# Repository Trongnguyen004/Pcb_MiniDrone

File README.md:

# Pcb_MiniDrone
### #Hình ảnh

<p align="center">
  <table>
    <tr>
      <td>
        
      </td>
      <td>
        
      </td>
    </tr>
  </table>
</p>

### #3D

<p align="center">
  <table>
    <tr>
      <td>
        
      </td>
      <td>
        
      </td>
      <td>
        
      </td>
    </tr>
  </table>
</p>

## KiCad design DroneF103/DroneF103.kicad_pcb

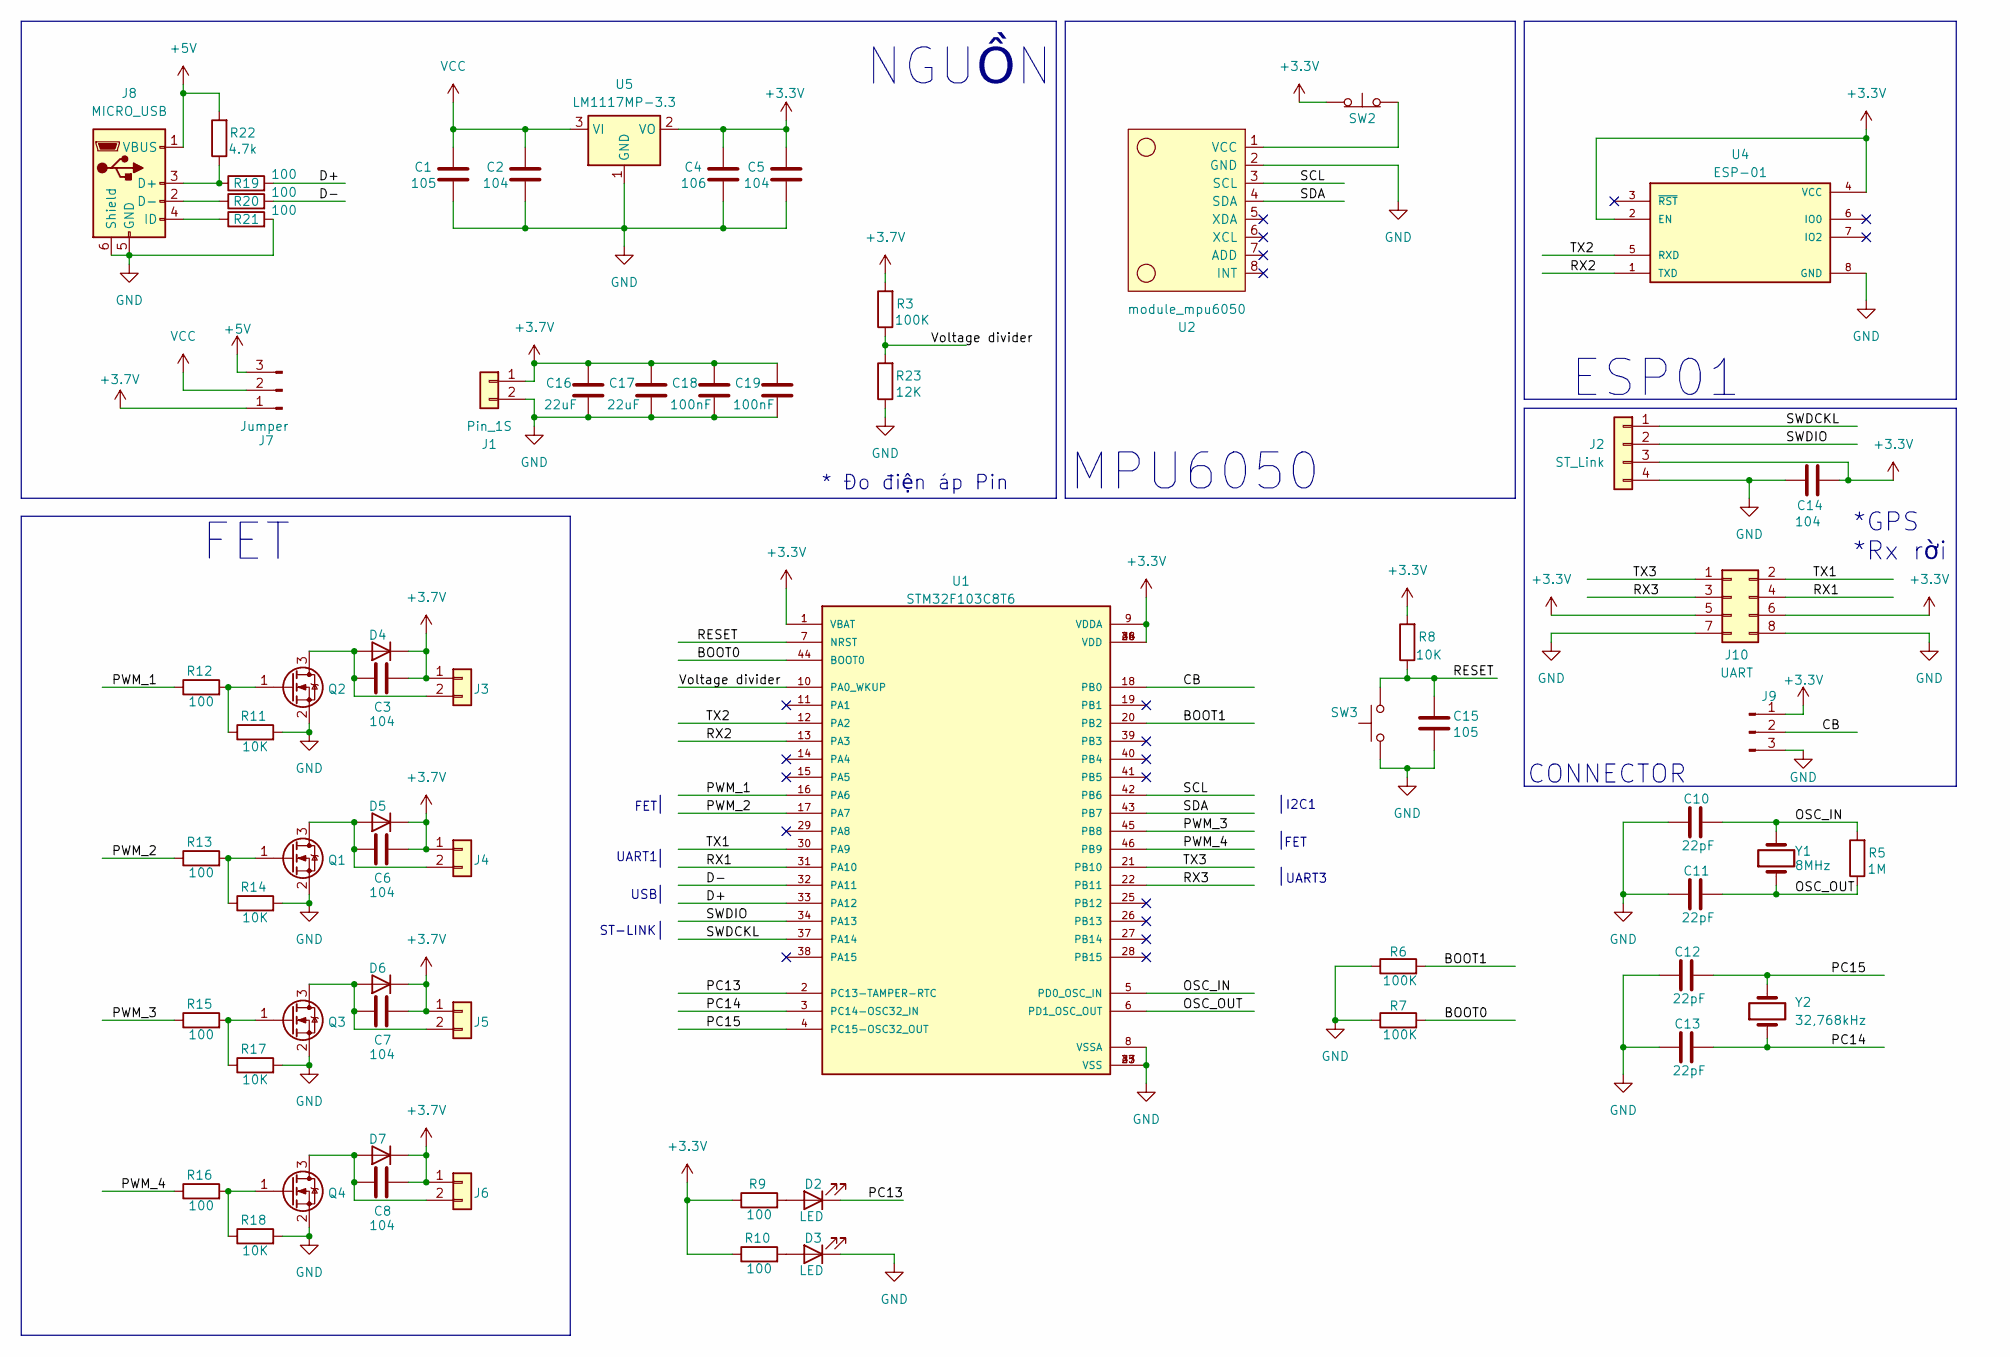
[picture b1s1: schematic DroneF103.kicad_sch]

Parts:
C1, C15: 105; C_0805_2012Metric
C2, C3, C5, C6, C7, C8, C14: 104; C_0805_2012Metric
C4: 106; C_0805_2012Metric
C10, C11, C12, C13: 22pF; C_0805_2012Metric
C16, C17: 22uF; C_0805_2012Metric
C18, C19: 100nF; C_0805_2012Metric
D2, D3: LED; LED_0805_2012Metric
D4, D5, D6, D7: 1N4007; D_SMA
J1: Pin_1S; JST_B2B-XH-A_LF__SN_
J2: ST_Link; PinHeader_1x04_P2.54mm_Vertical
J3, J4, J5, J6: Header; JST_B2B-XH-A_LF__SN_
J7: Jumper; PinHeader_1x03_P2.54mm_Vertical
J8: MICRO_USB; HRS_ZX62D-B-5P8
J9: Conn_01x03_Pin; PinHeader_1x03_P2.54mm_Vertical
J10: UART; PinHeader_2x04_P2.54mm_Vertical
Q1, Q2, Q3, Q4: IRLM0030; SOT95P237X112-3N
R3, R6, R7: 100K; R_0805_2012Metric
R5: 1M; R_0805_2012Metric
R8, R11, R14, R17, R18: 10K; R_0805_2012Metric
R9, R10, R12, R13, R15, R16, R19, R20, R21: 100; R_0805_2012Metric
R22: 4.7k; R_0805_2012Metric
R23: 12K; R_0805_2012Metric
SW2: SW_Push_Open; SW_SPST_B3U-1000P-B
SW3: SW_Push; SW_SPST_B3U-1000P-B
U1: STM32F103C8T6; QFP50P900X900X160-48N; PARTREV 10
U2: module_mpu6050
U4: ESP-01; XCVR_ESP8266-01_ESP-01; PARTREV V1.2
U5: LM1117MP-3.3; SOT-223-3_TabPin2
Y1: 8MHz; Crystal_HC49-4H_Vertical
Y2: 32,768kHz; XTAL_AB38T-32.768KHZ

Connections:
+3.3V: C4.1, C5.1, C14.1, J2.3, J9.1, J10.5, J10.6, R8.2, R9.1, R10.1, SW2.1 (A), U1.1 (VBAT), U1.9 (VDDA), U1.24 (VDD), U1.36 (VDD), U1.48 (VDD), U4.2 (EN), U4.4 (VCC), U5.2 (VO)
+3.7V: C3.2, C6.2, C7.2, C8.2, C16.1, C17.1, C18.1, C19.1, D4.1 (K), D5.1 (K), D6.1 (K), D7.1 (K), J1.1, J3.1, J4.1, J5.1, J6.1, J7.1, R3.2
+5V: J7.3, J8.1 (VBUS), R22.2
/BOOT0: R7.2, U1.44 (BOOT0)
/BOOT1: R6.2, U1.20 (PB2)
/CB: J9.2, U1.18 (PB0)
/D+: R19.2, U1.33 (PA12)
/D-: R20.2, U1.32 (PA11)
/OSC_IN: C10.1, R5.2, U1.5 (PD0_OSC_IN), Y1.2
/OSC_OUT: C11.1, R5.1, U1.6 (PD1_OSC_OUT), Y1.1
/PC13: D2.1 (K), U1.2 (PC13-TAMPER-RTC)
/PC14: C13.1, U1.3 (PC14-OSC32_IN), Y2.1
/PC15: C12.1, U1.4 (PC15-OSC32_OUT), Y2.2
/PWM_1: R12.1, U1.16 (PA6)
/PWM_2: R13.1, U1.17 (PA7)
/PWM_3: R15.1, U1.45 (PB8)
/PWM_4: R16.1, U1.46 (PB9)
/RESET: C15.1, R8.1, SW3.2, U1.7 (NRST)
/RX1: J10.4, U1.31 (PA10)
/RX2: U1.13 (PA3), U4.1 (TXD)
/RX3: J10.3, U1.22 (PB11)
/SCL: U1.42 (PB6), U2.3 (SCL)
/SDA: U1.43 (PB7), U2.4 (SDA)
/SWDCKL: J2.1, U1.37 (PA14)
/SWDIO: J2.2, U1.34 (PA13)
/TX1: J10.2, U1.30 (PA9)
/TX2: U1.12 (PA2), U4.5 (RXD)
/TX3: J10.1, U1.21 (PB10)
/Voltage divider: R3.1, R23.2, U1.10 (PA0_WKUP)
GND: C1.2, C2.2, C4.2, C5.2, C10.2, C11.2, C12.2, C13.2, C14.2, C15.2, C16.2, C17.2, C18.2, C19.2, D3.1 (K), J1.2, J2.4, J8.5 (GND), J8.6 (Shield), J9.3, J10.7, J10.8, Q1.2 (S), Q2.2 (S), Q3.2 (S), Q4.2 (S), R6.1, R7.1, R11.2, R14.2, R17.2, R18.2, R21.2, R23.1, SW3.1, U1.8 (VSSA), U1.23 (VSS), U1.35 (VSS), U1.47 (VSS), U2.2 (GND), U4.8 (GND), U5.1 (GND)
unnamed: D2.2 (A), R9.2
unnamed: D3.2 (A), R10.2
unnamed: C3.1, D4.2 (A), J3.2, Q2.3 (D)
unnamed: C6.1, D5.2 (A), J4.2, Q1.3 (D)
unnamed: C7.1, D6.2 (A), J5.2, Q3.3 (D)
unnamed: C8.1, D7.2 (A), J6.2, Q4.3 (D)
unnamed: J8.3 (D+), R19.1, R22.1
unnamed: J8.2 (D-), R20.1
unnamed: J8.4 (ID), R21.1
unnamed: Q1.1 (G), R13.2, R14.1
unnamed: Q2.1 (G), R11.1, R12.2
unnamed: Q3.1 (G), R15.2, R17.1
unnamed: Q4.1 (G), R16.2, R18.1
unnamed: SW2.2 (B), U2.1 (VCC)
VCC: C1.1, C2.1, J7.2, U5.3 (VI)

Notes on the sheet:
*GPS *Rx rời
* Đo điện áp Pin
USB
NGUỒN
ESP01
CONNECTOR
FET
MPU6050
ST-LINK
UART3
UART1
I2C1

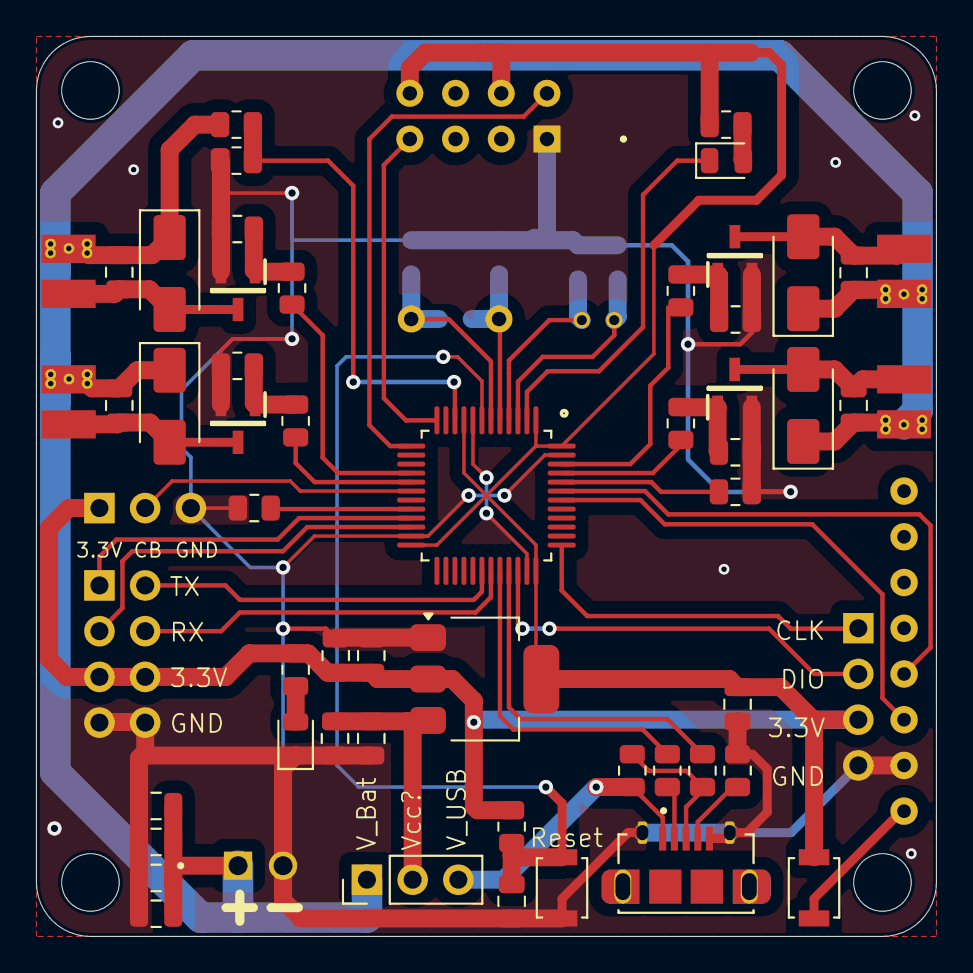
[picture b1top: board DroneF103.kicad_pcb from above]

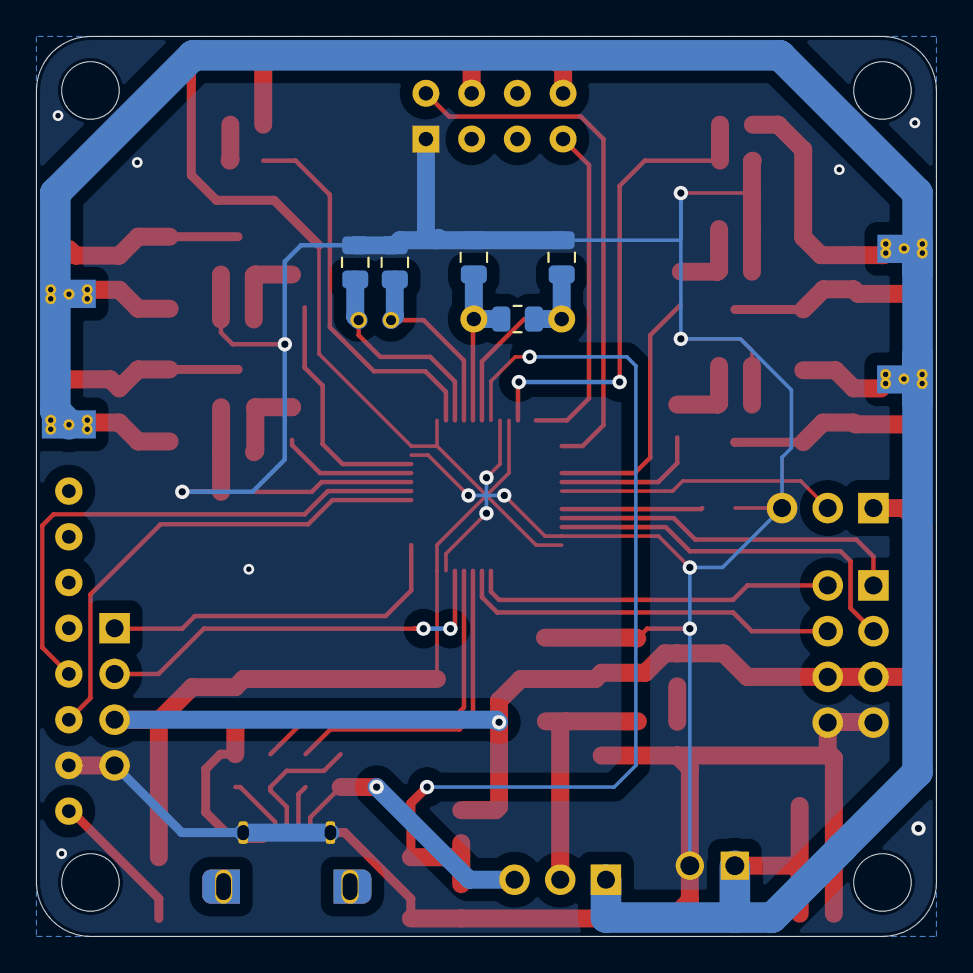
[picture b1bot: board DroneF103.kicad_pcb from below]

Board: 2 copper layers, 50.0 x 50.0 mm, 66 parts (5 on the bottom side), 45 nets.
